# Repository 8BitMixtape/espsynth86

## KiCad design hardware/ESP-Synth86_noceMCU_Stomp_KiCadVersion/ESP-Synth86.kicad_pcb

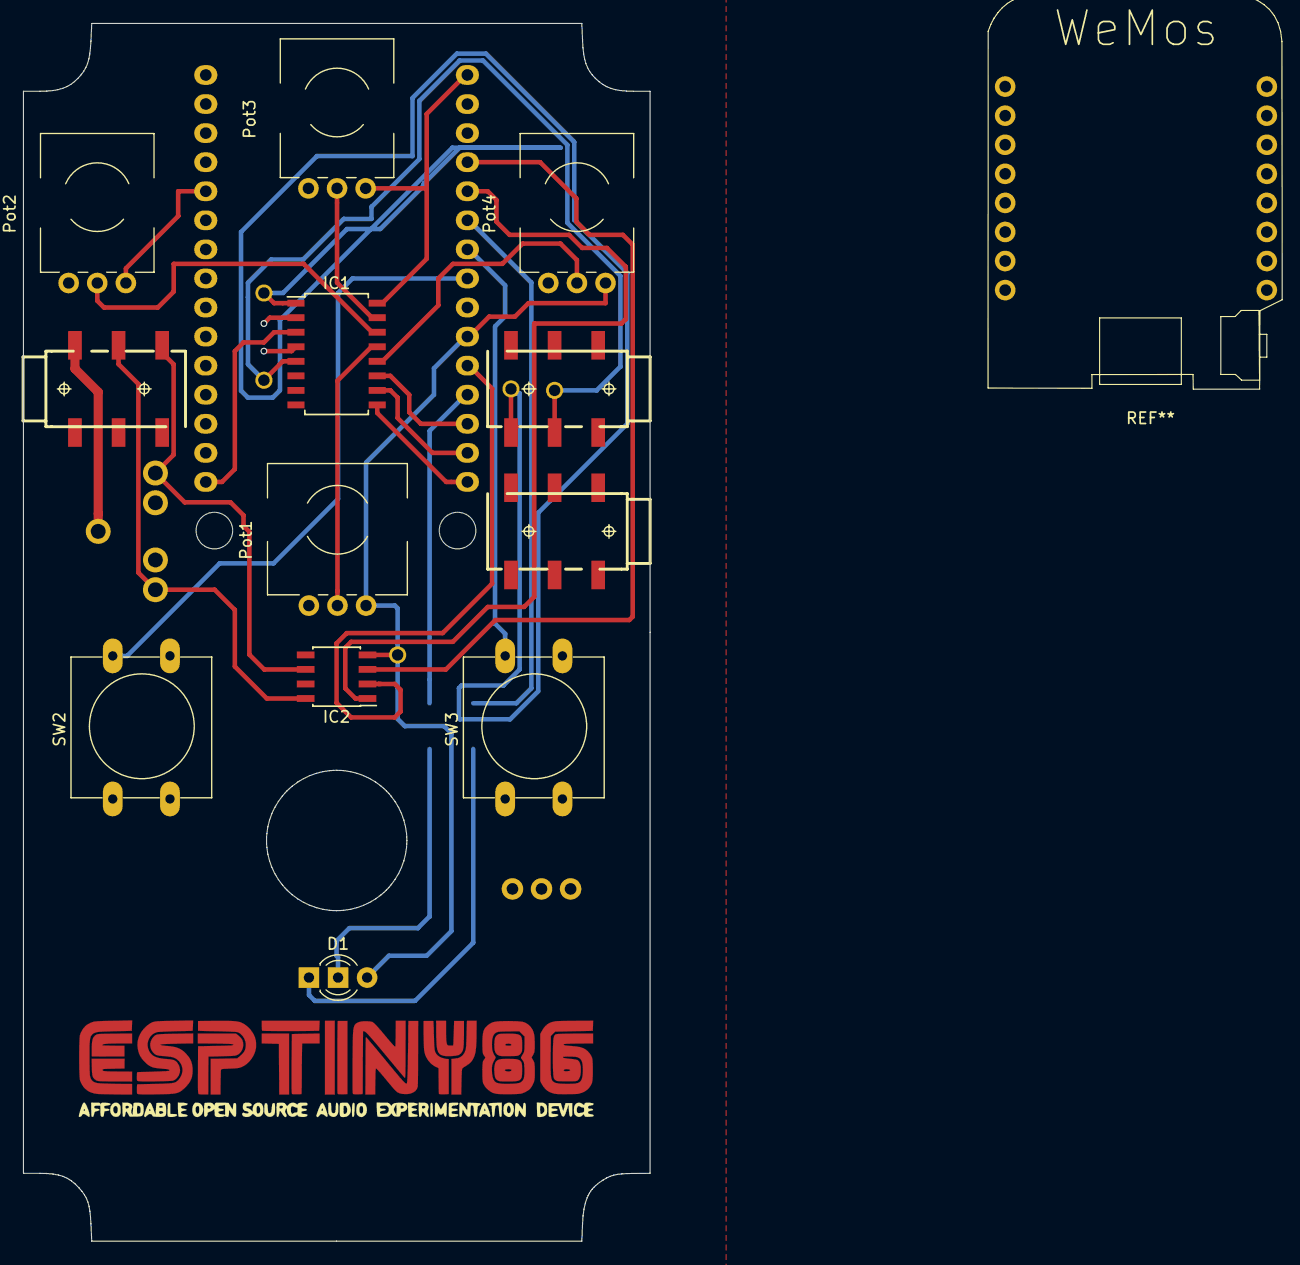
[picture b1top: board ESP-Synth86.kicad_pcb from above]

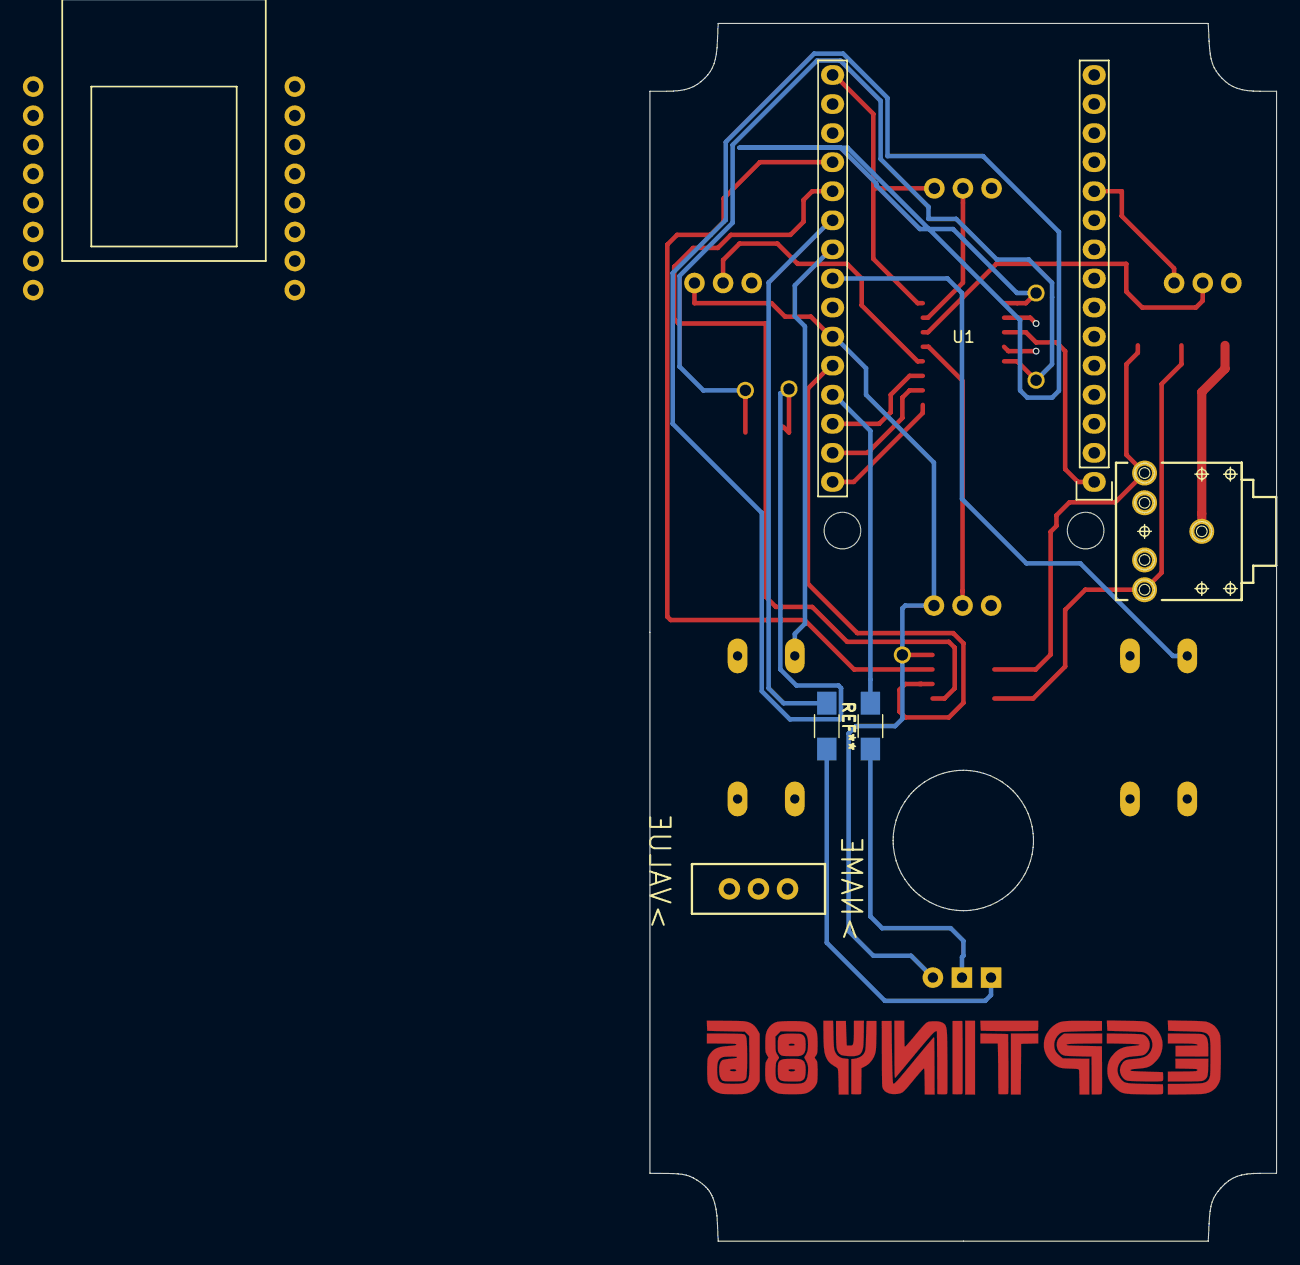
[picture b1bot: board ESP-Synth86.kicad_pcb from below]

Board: 2 copper layers, 54.8 x 106.4 mm, 15 parts (2 on the bottom side), 19 nets.

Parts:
>NAME: >VALUE; SWITCH-SPDT
D1: LED_Dual_CCA; Stomp_LED-Ring_DUAL
IC1: 4051; SOIC-16W_5.3x10.2mm_Pitch1.27mm
IC2: DAC7513_DCN; SOIC-8_3.9x4.9mm_Pitch1.27mm
Jack1: JACK_TRS_6PINS; AUDIO-Jack_3.5mm_5Pin
Jack1#2, Jack2, Jack3: JACK_TRS_6PINS; AUDIO-JACK-3.5mm_SMD
Pot1: 10k_big; Mixtape_Pot_Alps_RK09L_Sleve_Single_Horizontal
Pot2, Pot3, Pot4: 10k; Mixtape_Pot_Alps_RK09K_Horizontal
SW2, SW3: SW_Push; SW_PUSH-12mm_3D
U1: NodeMCU_1.0_(ESP-12E); NodeMCU_Amica_R2

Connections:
+3V3: D1.3, IC1.16, IC2.4, Pot1.1, Pot2.1, Pot3.1, Pot4.1, U1.11, U1.16, U1.25
/PDS: IC2.3, U1.19
Button1: SW2.1, U1.23
Button2: SW3.1, U1.22
CV1: IC1.1, Jack3.2
CV2: IC1.5, Jack3.3
GND: IC1.6, IC1.7, IC1.8, IC2.5, Jack1.1, Jack1#2.1, Jack2.1, Jack3.1, Pot1.3, Pot2.3, Pot3.3, Pot4.3, SW2.2, SW3.2, U1.10, U1.14, U1.17, U1.24
L-Out: IC2.6, Jack1.2, Jack1#2.2
unnamed: IC1.3, U1.1
unnamed: IC1.9, U1.30
unnamed: IC1.10, U1.29
unnamed: IC1.11, U1.28
unnamed: IC2.1, U1.20
unnamed: IC2.2, U1.26
Pot1: IC1.13, Pot1.2
Pot2: IC1.14, Pot2.2
Pot3: IC1.15, Pot3.2
Pot4: IC1.12, Pot4.2
R-Out: IC2.8, Jack1.3, Jack1#2.3

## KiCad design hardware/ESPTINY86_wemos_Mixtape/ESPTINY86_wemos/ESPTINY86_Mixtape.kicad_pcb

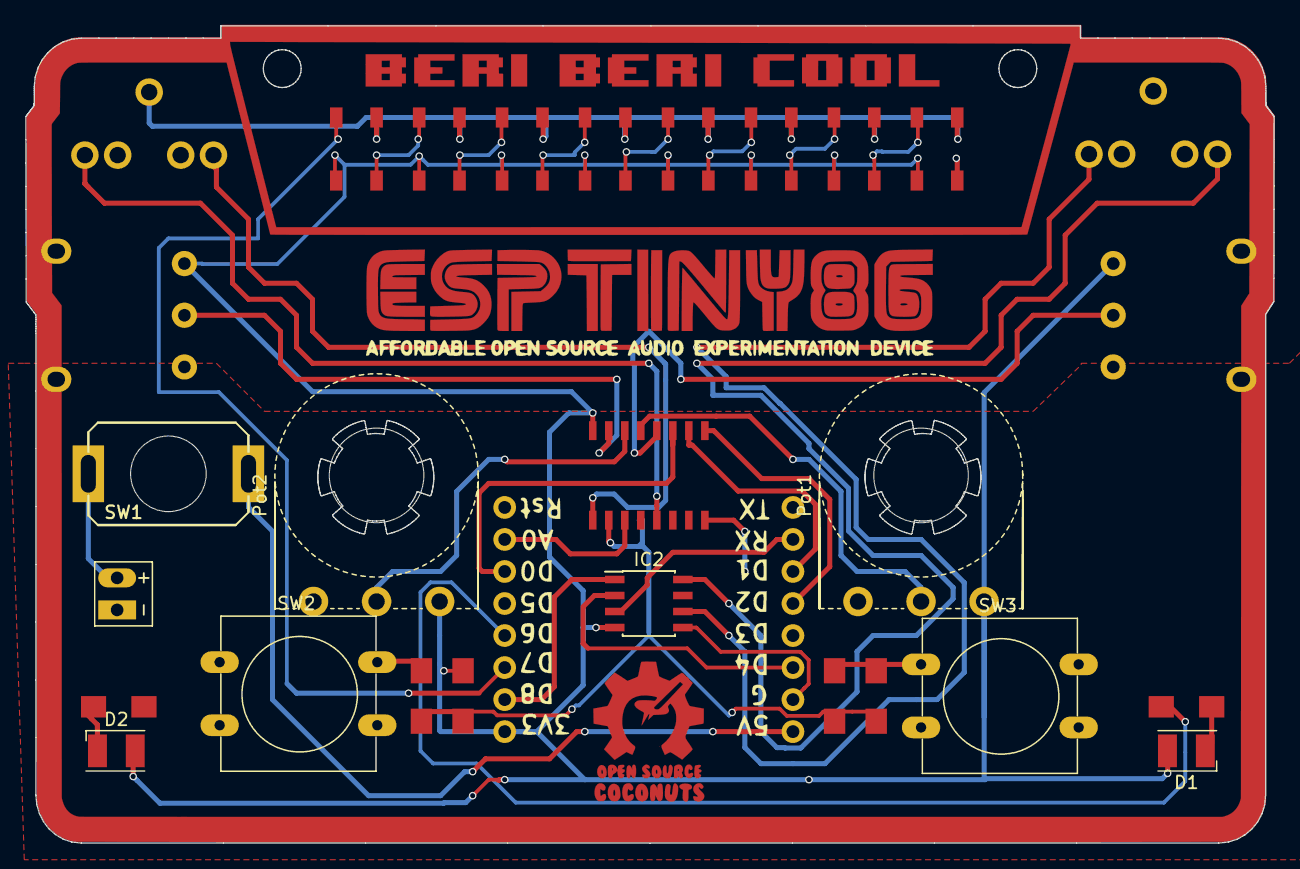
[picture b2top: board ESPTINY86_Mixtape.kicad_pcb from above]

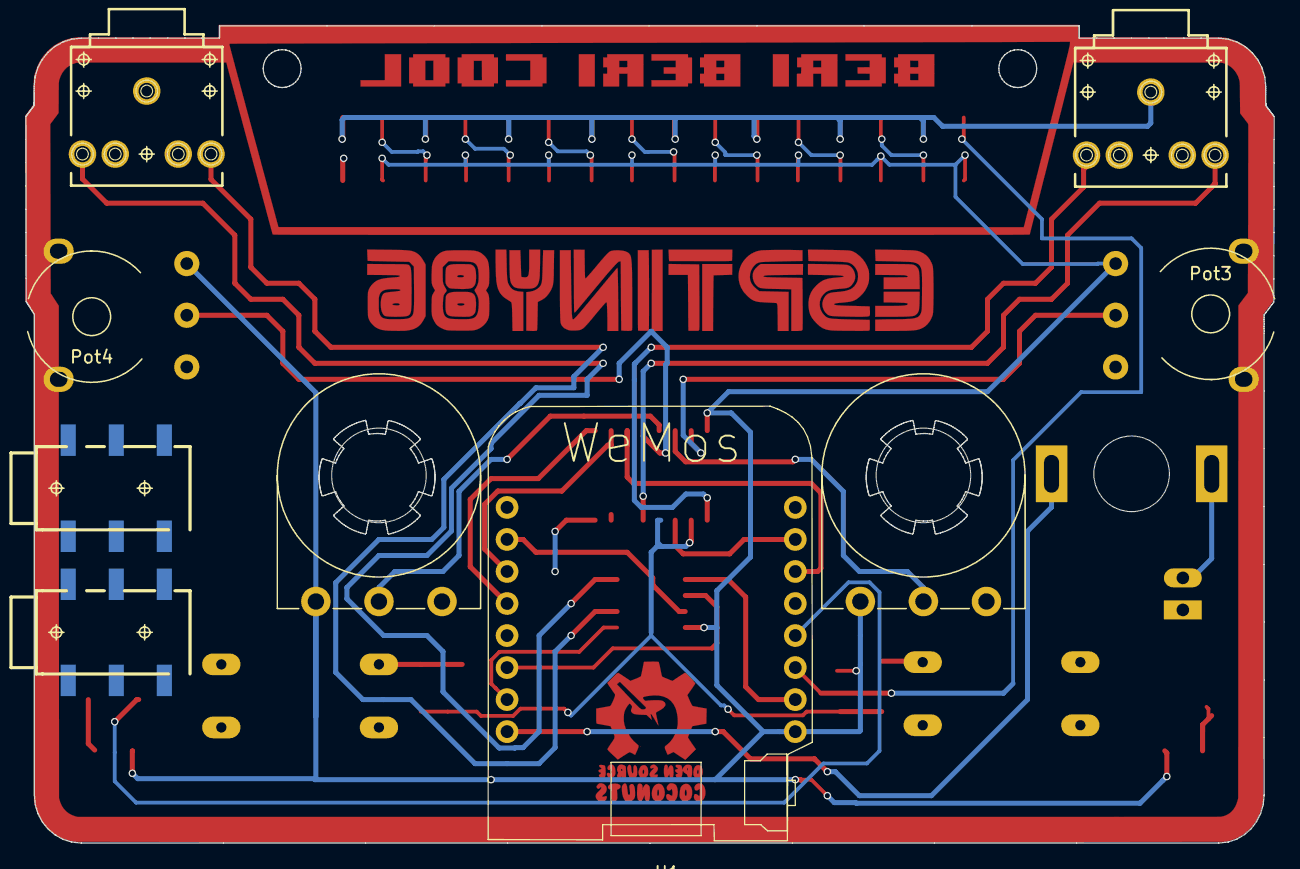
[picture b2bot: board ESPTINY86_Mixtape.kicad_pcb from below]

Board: 2 copper layers, 99.0 x 64.8 mm, 33 parts (7 on the bottom side), 33 nets.

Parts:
Coconut: LOGO; Coconut_Logo_small_Mask
Coconut#2: LOGO; Coconut_Logo_small
D1, D2: LED; TopLED_2835
IC1: 4051; 4xxx_SOIC-16W_Pitch1.27mm
IC2: DAC7513_DCN; SOIC-8_3.9x4.9mm_Pitch1.27mm
J1: Bat_EXT; Bat_connector+-
Jack1, Jack3: JACK_TRS_6PINS; AUDIO-Jack_3.5mm_5Pin
Jack2, Jack2#2: JACK_TRS_6PINS; AUDIO-JACK-3.5mm_SMD
NEO1, NEO2, NEO3, NEO4, NEO5, NEO6, NEO7, NEO8: LED_SK6813; Mixtape_NEO_WS2812B
Pot1: 10k_big; Potentiometer_Piher_T16L_Single_Horizontal_MountLS
Pot2: 10k; Potentiometer_Piher_T16L_Single_Horizontal_MountLS
Pot3, Pot4: 10k; Potentiometer_wheel
R1, R2: R; R_1206_Mixtape
R3, R3#2: 22k; R_1206_Mixtape
R4, R5: 10k; R_1206_Mixtape
SW1: SW_SPST; Push_SWITCH_hole
SW2, SW3: SW_Push; SW_PUSH-12mm_3D
U1: WeMos_mini; WeMOS_ESP

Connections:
+3V3: D1.2, D2.2, IC1.16, IC2.4, NEO1.1, NEO2.1, NEO3.1, NEO4.1, NEO5.1, NEO6.1, NEO7.1, NEO8.1, Pot1.1, Pot2.1, Pot3.1, Pot4.1, R4.1, U1.16
+5V: SW1.2, U1.1
+BATT: J1.1, SW1.1
/PDS: IC2.3, U1.7
Button1: IC1.2, IC1.4, R3.2, R3#2.2, R4.2, R5.2
CV1: IC1.1, Jack3.2
CV2: IC1.5, Jack3.3
GND: IC1.6, IC1.7, IC1.8, IC2.5, J1.2, Jack1.1, Jack2.1, Jack2#2.1, Jack3.1, NEO1.3, NEO2.3, NEO3.3, NEO4.3, NEO5.3, NEO6.3, NEO7.3, NEO8.3, Pot1.3, Pot2.3, Pot3.3, Pot4.3, R2.1, SW2.2, SW3.2, U1.2
L-Out: IC2.6, Jack1.3
Led1_pulldown: R1.2, U1.13
NEO-Pixel: NEO8.4, U1.14
unnamed: D1.1, R1.1
unnamed: D2.1, R2.2
unnamed: IC1.3, U1.10
unnamed: IC1.9, U1.5
unnamed: IC1.10, U1.6
unnamed: IC1.11, U1.11
unnamed: IC2.1, U1.15
unnamed: IC2.2, U1.3
unnamed: NEO1.4, NEO2.2
unnamed: NEO2.4, NEO3.2
unnamed: NEO3.4, NEO4.2
unnamed: NEO4.4, NEO5.2
unnamed: NEO5.4, NEO6.2
unnamed: NEO6.4, NEO7.2
unnamed: NEO7.4, NEO8.2
unnamed: R3.1, R3#2.1, SW3.1
unnamed: R5.1, SW2.1
Pot1: IC1.13, Pot1.2
Pot2: IC1.14, Pot2.2
Pot3: IC1.15, Pot3.2
Pot4: IC1.12, Pot4.2
R-Out: IC2.8, Jack1.2

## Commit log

2018-07-19 dusjagr's changes
2018-07-22 dusjagr geeking
2018-07-26 LED!
2018-08-01 changed button schematic
